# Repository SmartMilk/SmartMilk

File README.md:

# SmartMilk: an automated milk monitoring system
 
SmartMilk is a simple temperature dependent system for monitoring the condition of your milk. When milk has been left out of the fridge SmartMilk will notify the users smartphone of the condition of their milk over time, to help prevent the need for disposing of spoiled milk. 

The system has been designed to be simple, yet robust, and can be run on a Raspberry Pi (RPi). 
This repository contains the software, and associated instructions, required to implement the SmartMilk application for your own use. 

For a detailed description of the project, and information on the hardware, libraries and packages required for getting it working, please refer to our Wiki. Installation instructions are provided below.

SmartMilk was developed as part of the Real Time Embedded Programming module at the University of Glasgow.

# Making it work
To clone this git repository: 
```
git clone https://github.com/SmartMilk/SmartMilk.git
```

To make the smartphone notification subsystem executable:
```
cd SmartMilk
sudo chmod u+x prowl1.pl prowl2.pl prowl3.pl
```

Now build the main software by typing:
```
qmake
make
```

To run (assuming you are logged into the RPi over ssh and no X-server is running):
```
startx ./SmartMilkApp
```

or with X running:
```
./SmartMilkApp
```

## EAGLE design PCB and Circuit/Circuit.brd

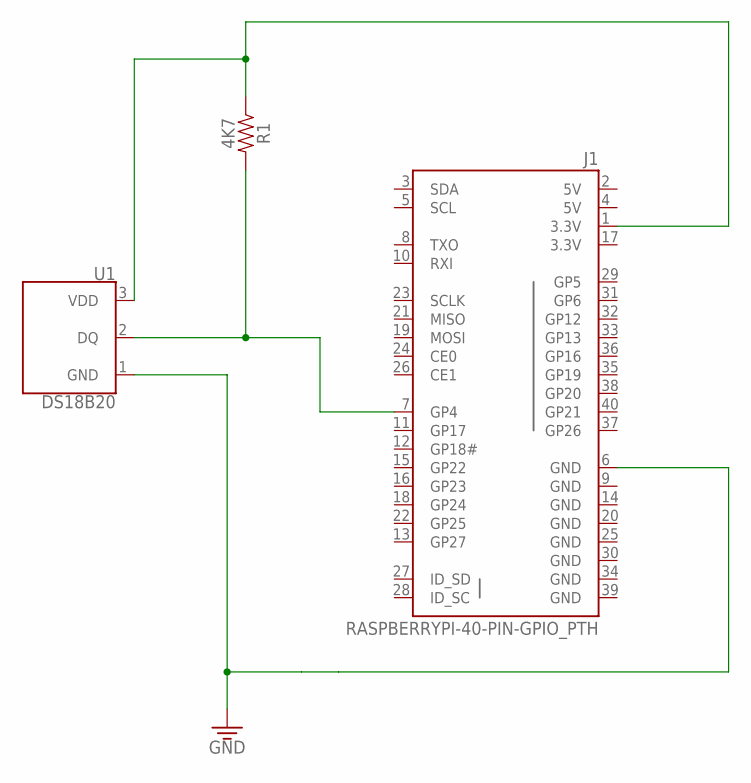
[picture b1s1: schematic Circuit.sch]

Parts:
J1: RASPBERRYPI-40-PIN-GPIO_PTH; 2X20_SHROUDED
R1: 4K7; AXIAL-0.3
U1: DS18B20; TO-92-AMMO

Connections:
3.3V: J1.6 (GND), J1.17 (3.3V), U1.1 (GND)
5V: J1.2 (5V), J1.4 (5V)
GND: J1.9 (GND), J1.14 (GND), J1.20 (GND), J1.25 (GND), J1.30 (GND), J1.34 (GND), J1.39 (GND)
unnamed: J1.1 (3.3V), R1.P$1 (1), U1.3 (VDD)
unnamed: J1.7 (GP4), R1.P$2 (2), U1.2 (DQ)

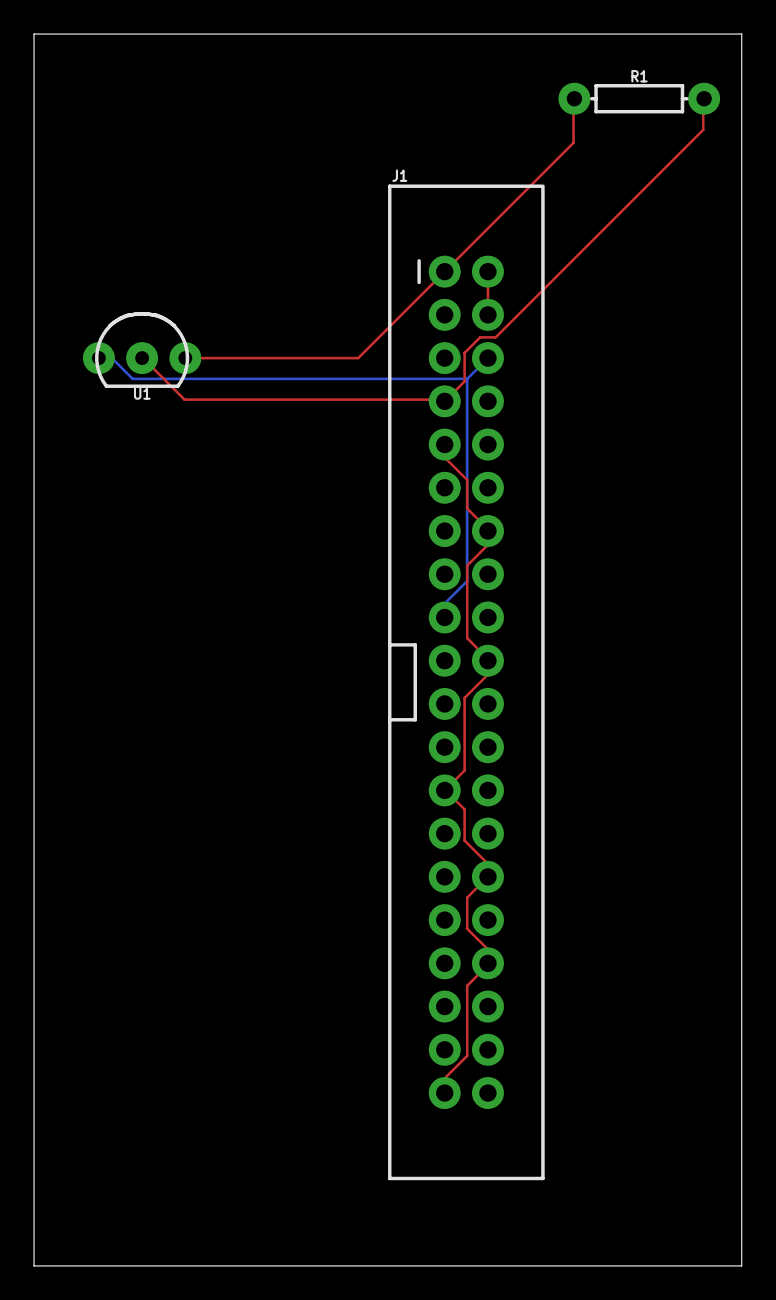
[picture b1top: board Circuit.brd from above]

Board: 2 copper layers, 41.6 x 72.4 mm, 3 parts (0 on the bottom side), 5 nets.

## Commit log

2018-02-26 Added some more comments to some of the functions
2018-02-26 Added our RPi device name for d_name
2018-02-26 Ignore
    Ignore this
2018-02-27 Set theme jekyll-theme-hacker
2018-02-28 Now with proper name and extension
2018-03-01 Commented CppTimer.h include
2018-03-02 Commented CppTimer.h
2018-03-12 Update window.cpp
    Fixed .png files and Celsius/Farenheit button names
2018-03-13 v2 hopefully
    Added timer functionality (uncompiled)
2018-03-13 Update window.h
    moved variable definitions to header
2018-03-14 Functional QT timer
2018-03-15 This is SmartMilkv3 (updated on 14/03/2018)
    Updates from previous version mostly of window.cpp, and the startCountdown() function:
    - includes the timer intervals and message prompts needed for testing
    - temperature thresholds (i.e. milk, fridge, and room temp) added, and coloured using QPen library
    - (commented) shell script call from window.cpp to execute prowl1.pl for alerting iPhone app
    window.h also updated with new variables/thresholds etc
2018-03-15 For communicating between Prowl app and window.cpp
2018-03-16 v 3.1
    trialling different aspects of timer and GUI plotting
2018-03-17 Organised repository
2018-03-20 comments
2018-03-20 preparing for buttons
2018-03-20 Added button functionality (untested)
2018-03-25 Update window.cpp
    - Changed 'createCountdownBox()' to 'createMessageBox()'
    - Included message labels within 'createMessageBox()'
    - Set colour activation for the three messages within 'startCountdown()'
    - Changed the 'reading' QLabel to display user warnings instead of clock time. these are specified within 'startCountdown()' too
2018-03-25 Update window.h
    Added in the new labels and updated names. Removed pointless labels and buttons, and replaced with relevant ones. Added QVBoxLayout *layout to private.
2018-03-26 For SmartMilkv4
    Changed createCountdownBox() to createMessageBox().
    Created three message labels with colour activation.
    Changed countdown label to user information label (i.e. reading).
2018-03-26 For SmartMilkv4
2018-03-26 Final repository changes
2018-03-26 Changed TARGET to SmartMilkv4
2018-03-26 Added threshold conversions to setDegC() and setDegF()
2018-03-26 Fixed return
2018-03-28 Reformatted countdown function (untested on rpi)
    Changes made:
    - condensed the farenheit and celsius threshold changes (via button activation) into 2 functions instead of 4
    - removed QTimer functionality with countdown function, instead the function is activated then slept for 1 second using Linux sleep commands
    - reformatted countdown 'if' statement hierarchy, will hopefully lead to improved performance
    - minor alterations to Qlabel statements
    - minor addition/alteration to comments
2018-03-28 update from pi
2018-03-28 working temp change thresholds
    -Thresholds now change with celsius/farenheit button press
    -Plot also changes colour
    -Still very slow :( Will try to reformat if statements into for/while loops
2018-03-28 This time update git instead of other way round
    now I understand why its called git
2018-03-29 Threading implementation (untested)
    -Now with a QThread for the updatePlot (previously named timerEvent) function. No idea if it works. Probably not.
    -Additionally have now implemented 2 extra boxes for timer status, just to check that the timers are running (i.e for testing).
2018-03-29 thread alteration
    alteration as in it disnae work
2018-04-05 Updated version
    - created shell scripts in window.cpp using #define
    - added gradient background code for plot
2018-04-08 Create empty
2018-04-09 Making sure these are up to date
2018-04-09 remove prowl script directory
2018-04-10 GUI improvements
    - Added Splash Screen
    - Added/improved colours
2018-04-10 Now with thread implementation #2(untested)
    - Now tempread function has become its own thread class
    - tempread also has its own header
    - minor code reformatting
    - moved the definition of the prowl scripts from window.cpp to window.h
    - plotUpdate() is back to a QTimerEvent
    - Updated the .pro file to include the new .cpp and .h files
2018-04-10 more thread work
    thread appears to work but tempread no longer running endlessly, looking to rewrite this function
2018-04-10 re-formatted tempread function
2018-04-10 threads successfully implemented
    -Thread works (the thread intakes temperature readings)
    -No longer having the 'too many open files issue'
2018-04-11 Now with QTime (untested)
    - Should Display countdown to message sending
2018-04-11 Live timer successfully implemented
    - Replaced "timer started" status box with actual hh:mm:ss timer that counts down to message sending in real time
    - Reformatted timerCountdown() if-else statements for better operation
    - Project is essentially complete coding-wise
2018-04-13 Final version of window.cpp and window.h
2018-04-13 Changed message to send after 15mins instead of 30mins
2018-04-13 Final version
    TARGET changed to SmartMilkApp
2018-04-14 Final version of SmartMilkApp
2018-04-15 additional comments

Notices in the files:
parts and their libraries:
SparkFun-Connectors: Licensing: Creative Commons ShareAlike 4.0 International - https://creativecommons.org/licenses/by-sa/4.0
